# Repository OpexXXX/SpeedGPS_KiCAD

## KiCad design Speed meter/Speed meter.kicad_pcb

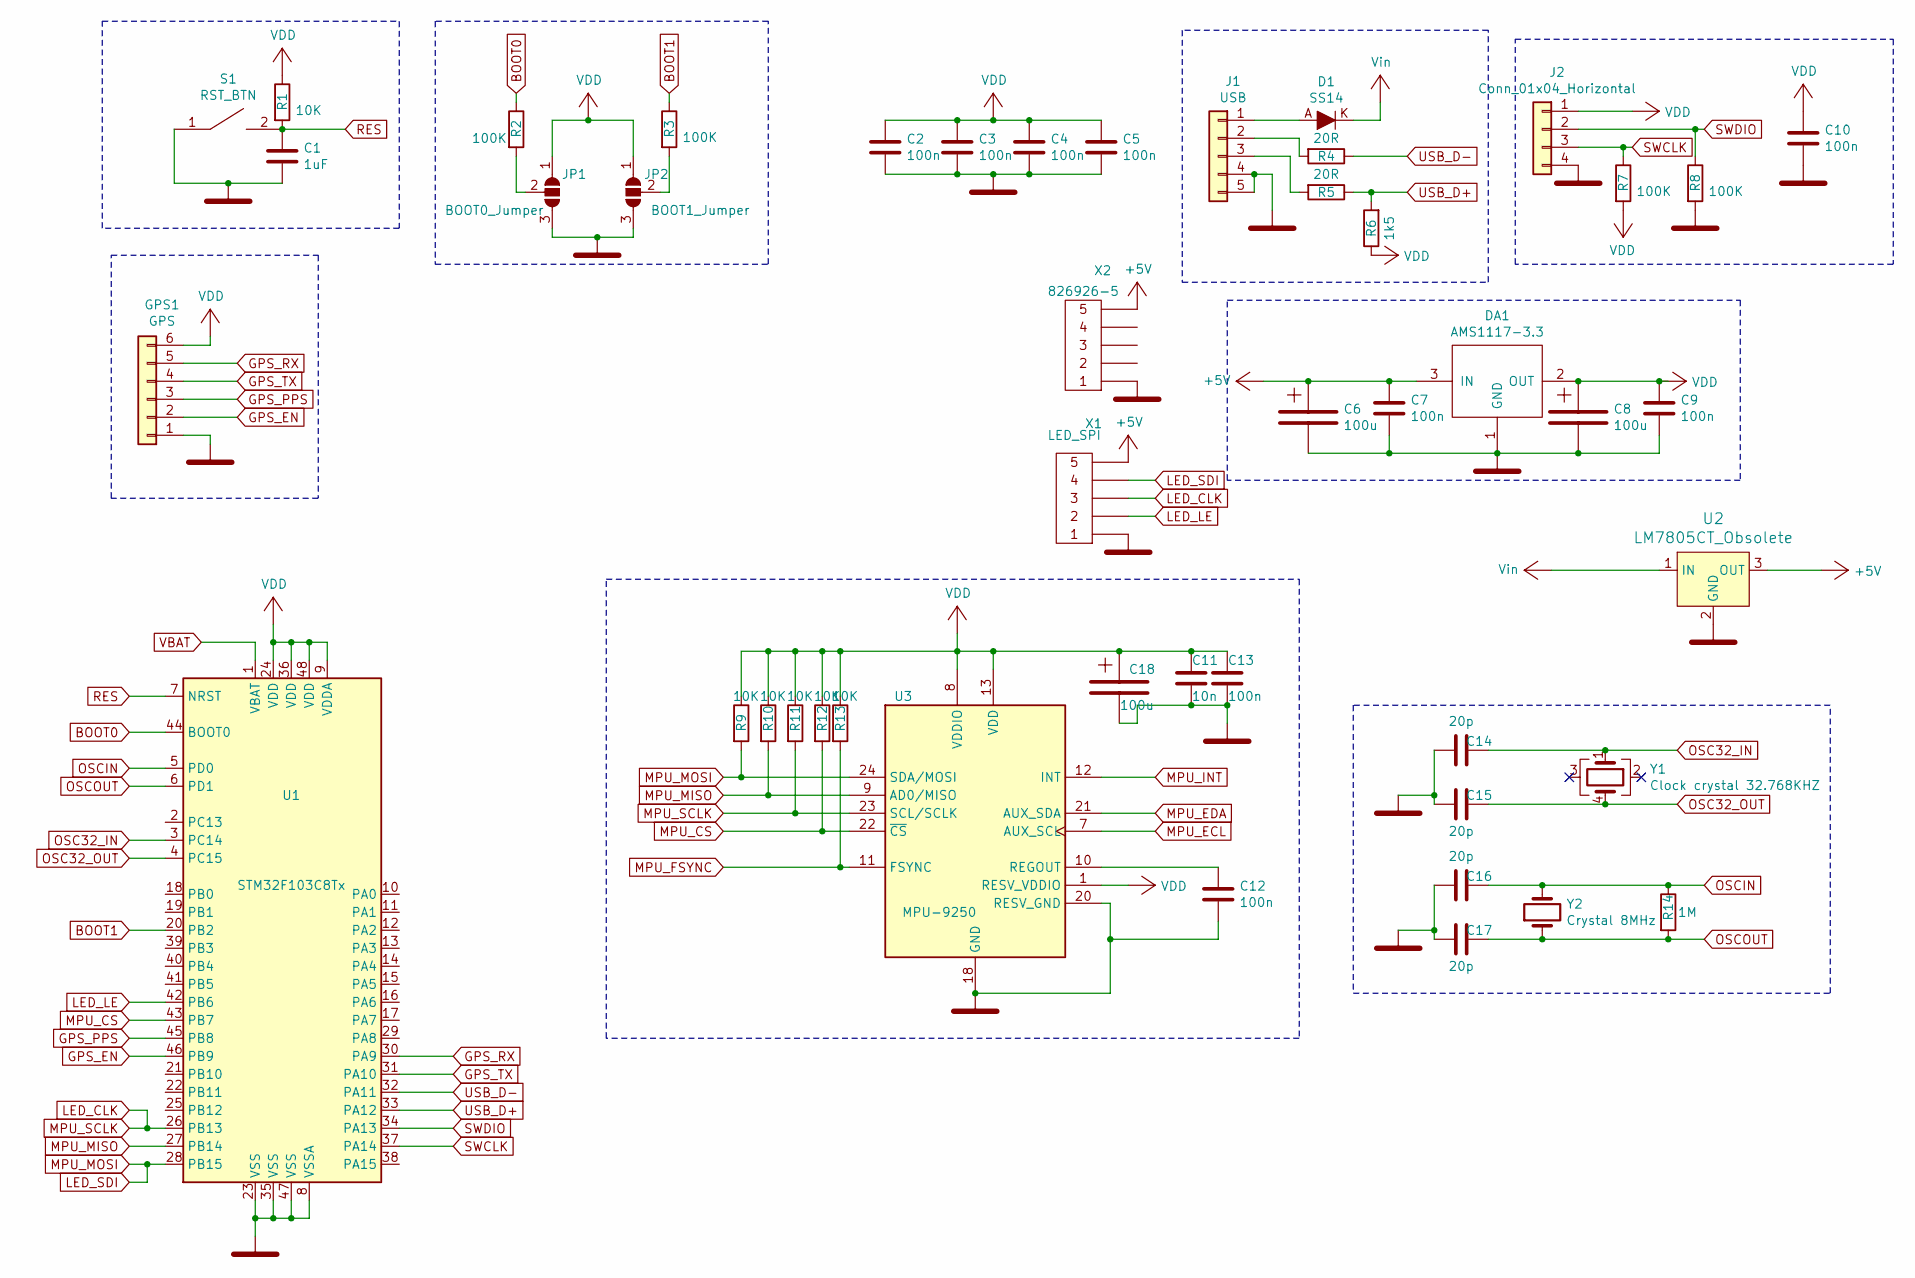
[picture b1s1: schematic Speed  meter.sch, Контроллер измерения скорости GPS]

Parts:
C1: 1uF; C_0603_1608Metric_Pad1.05x0.95mm_HandSolder
C2, C3, C4, C5, C7, C9, C10, C12, C13: 100n; C_0603_1608Metric_Pad1.05x0.95mm_HandSolder
C6, C8, C18: T491B107M010AT; CP_EIA-3528-15_AVX-H_Pad1.50x2.35mm_HandSolder
C11: 10n; C_0603_1608Metric_Pad1.05x0.95mm_HandSolder
C14, C15, C16, C17: 20p; C_0603_1608Metric_Pad1.05x0.95mm_HandSolder
D1: SS14; DO-214AC; MPN SS14; Digi-Key_PN SS14CT-ND
DA1: AMS1117-3.3; SOT-223
GPS1: GPS; PinHeader_2x03_P2.00mm_Vertical
J1: USB; PinHeader_1x05_P2.00mm_Vertical
J2: Conn_01x04_Horizontal; PinHeader_1x04_P2.54mm_Horizontal
JP1: BOOT0_Jumper; SolderJumper-3_P1.3mm_Open_RoundedPad1.0x1.5mm_NumberLabels
JP2: BOOT1_Jumper; SolderJumper-3_P1.3mm_Open_RoundedPad1.0x1.5mm_NumberLabels
R1, R9, R10, R11, R12, R13: 10K; R_0603_1608Metric_Pad1.05x0.95mm_HandSolder
R2, R3, R7, R8: 100K; R_0603_1608Metric_Pad1.05x0.95mm_HandSolder
R4, R5: 20R; R_0603_1608Metric_Pad1.05x0.95mm_HandSolder
R6: 1k5; R_0603_1608Metric_Pad1.05x0.95mm_HandSolder
R14: 1M; R_0603_1608Metric_Pad1.05x0.95mm_HandSolder
S1: RST_BTN; TS-1185-C-A-A
U1: STM32F103C8Tx; LQFP-48_7x7mm_P0.5mm
U2: LM7805CT_Obsolete; TO-220-3_Vertical; MPN LM7805CT; Digi-Key_PN LM7805CT-ND
U3: MPU-9250; InvenSense_QFN-24_3x3mm_P0.4mm
X1: LED_SPI; PinHeader_1x05_P2.54mm_Vertical
X2: 826926-5; PinHeader_1x05_P2.54mm_Vertical
Y1: Clock crystal 32.768KHZ; Oscillator_SMD_Fordahl_DFAS2-4Pin_7.3x5.1mm_HandSoldering
Y2: Crystal 8MHz; Crystal_HC18-U_Vertical

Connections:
+5V: C6.1, C7.1, DA1.3 (IN), U2.3 (OUT), X1.5, X2.5
BOOT0: R2.1, U1.44 (BOOT0)
BOOT1: R3.1, U1.20 (PB2)
GND: C1.2, C2.2, C3.2, C4.2, C5.2, C6.2, C7.2, C8.2, C9.2, C10.2, C11.2, C12.2, C13.2, C14.2, C15.2, C16.2, C17.2, C18.2, DA1.1 (GND), GPS1.1, J1.4, J1.5, J2.4, JP1.3 (B), JP2.3 (B), R8.2, S1.1, U1.8 (VSSA), U1.23 (VSS), U1.35 (VSS), U1.47 (VSS), U2.2 (GND), U3.18 (GND), U3.20 (RESV_GND), X1.1, X2.1
GPS_EN: GPS1.2, U1.46 (PB9)
GPS_PPS: GPS1.3, U1.45 (PB8)
GPS_RX: GPS1.5, U1.30 (PA9)
GPS_TX: GPS1.4, U1.31 (PA10)
LED_CLK: R11.2, U1.26 (PB13), U3.23 (SCL/SCLK), X1.3
LED_LE: U1.42 (PB6), X1.2
LED_SDI: R9.2, U1.28 (PB15), U3.24 (SDA/MOSI), X1.4
MPU_CS: R12.2, U1.43 (PB7), U3.22 (~CS)
MPU_ECL: U3.7 (AUX_SCL)
MPU_EDA: U3.21 (AUX_SDA)
MPU_FSYNC: R13.2, U3.11 (FSYNC)
MPU_INT: U3.12 (INT)
MPU_MISO: R10.2, U1.27 (PB14), U3.9 (AD0/MISO)
unnamed: C12.1, U3.10 (REGOUT)
unnamed: D1.A, J1.1
unnamed: J1.2, R4.2
unnamed: J1.3, R5.2
unnamed: JP1.2 (C), R2.2
unnamed: JP2.2 (C), R3.2
OSC32_IN: C14.1, U1.3 (PC14), Y1.1
OSC32_OUT: C15.1, U1.4 (PC15), Y1.4
OSCIN: C16.1, R14.1, U1.5 (PD0), Y2.2
OSCOUT: C17.1, R14.2, U1.6 (PD1), Y2.1
RES: C1.1, R1.2, S1.2, U1.7 (NRST)
SWCLK: J2.3, R7.1, U1.37 (PA14)
SWDIO: J2.2, R8.1, U1.34 (PA13)
USB_D+: R5.1, R6.2, U1.33 (PA12)
USB_D-: R4.1, U1.32 (PA11)
VBAT: U1.1 (VBAT)
VDD: C2.1, C3.1, C4.1, C5.1, C8.1, C9.1, C10.1, C11.1, C13.1, C18.1, DA1.2 (OUT), GPS1.6, J2.1, JP1.1 (A), JP2.1 (A), R1.1, R6.1, R7.2, R9.1, R10.1, R11.1, R12.1, R13.1, U1.9 (VDDA), U1.24 (VDD), U1.36 (VDD), U1.48 (VDD), U3.1 (RESV_VDDIO), U3.8 (VDDIO), U3.13 (VDD)
Vin: D1.K, U2.1 (IN)

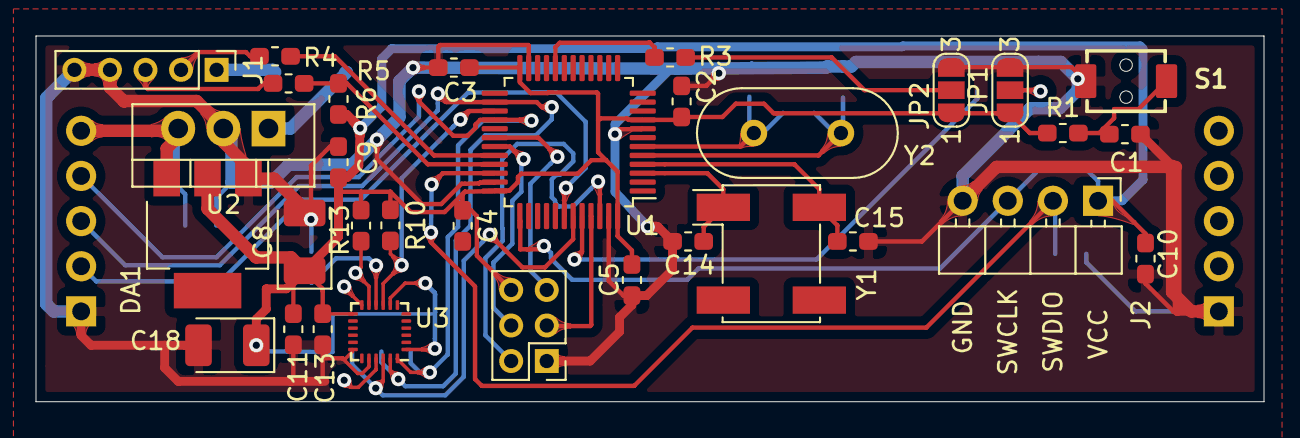
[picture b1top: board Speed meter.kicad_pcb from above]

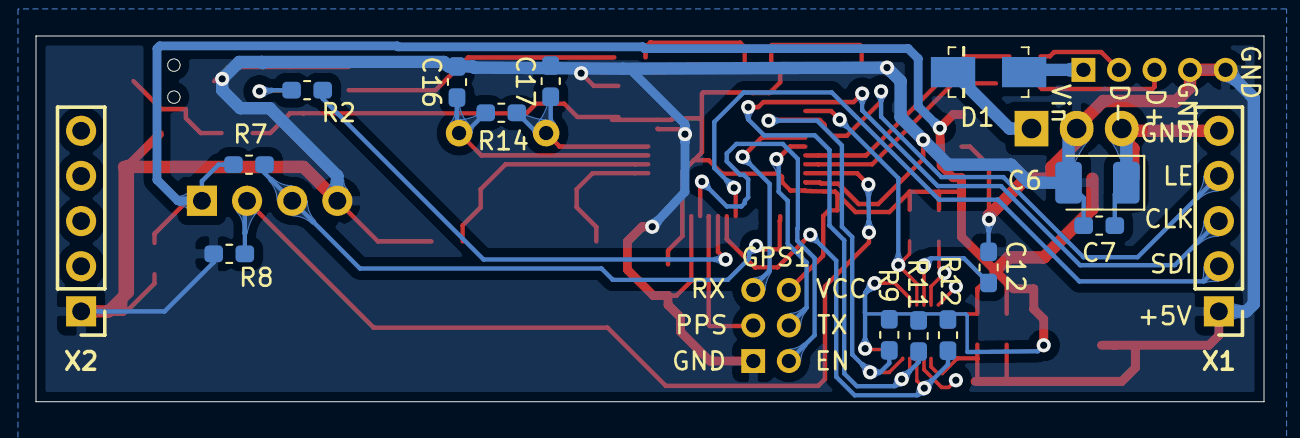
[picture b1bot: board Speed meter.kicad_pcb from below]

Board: 2 copper layers, 69.1 x 20.6 mm, 47 parts (15 on the bottom side), 31 nets.

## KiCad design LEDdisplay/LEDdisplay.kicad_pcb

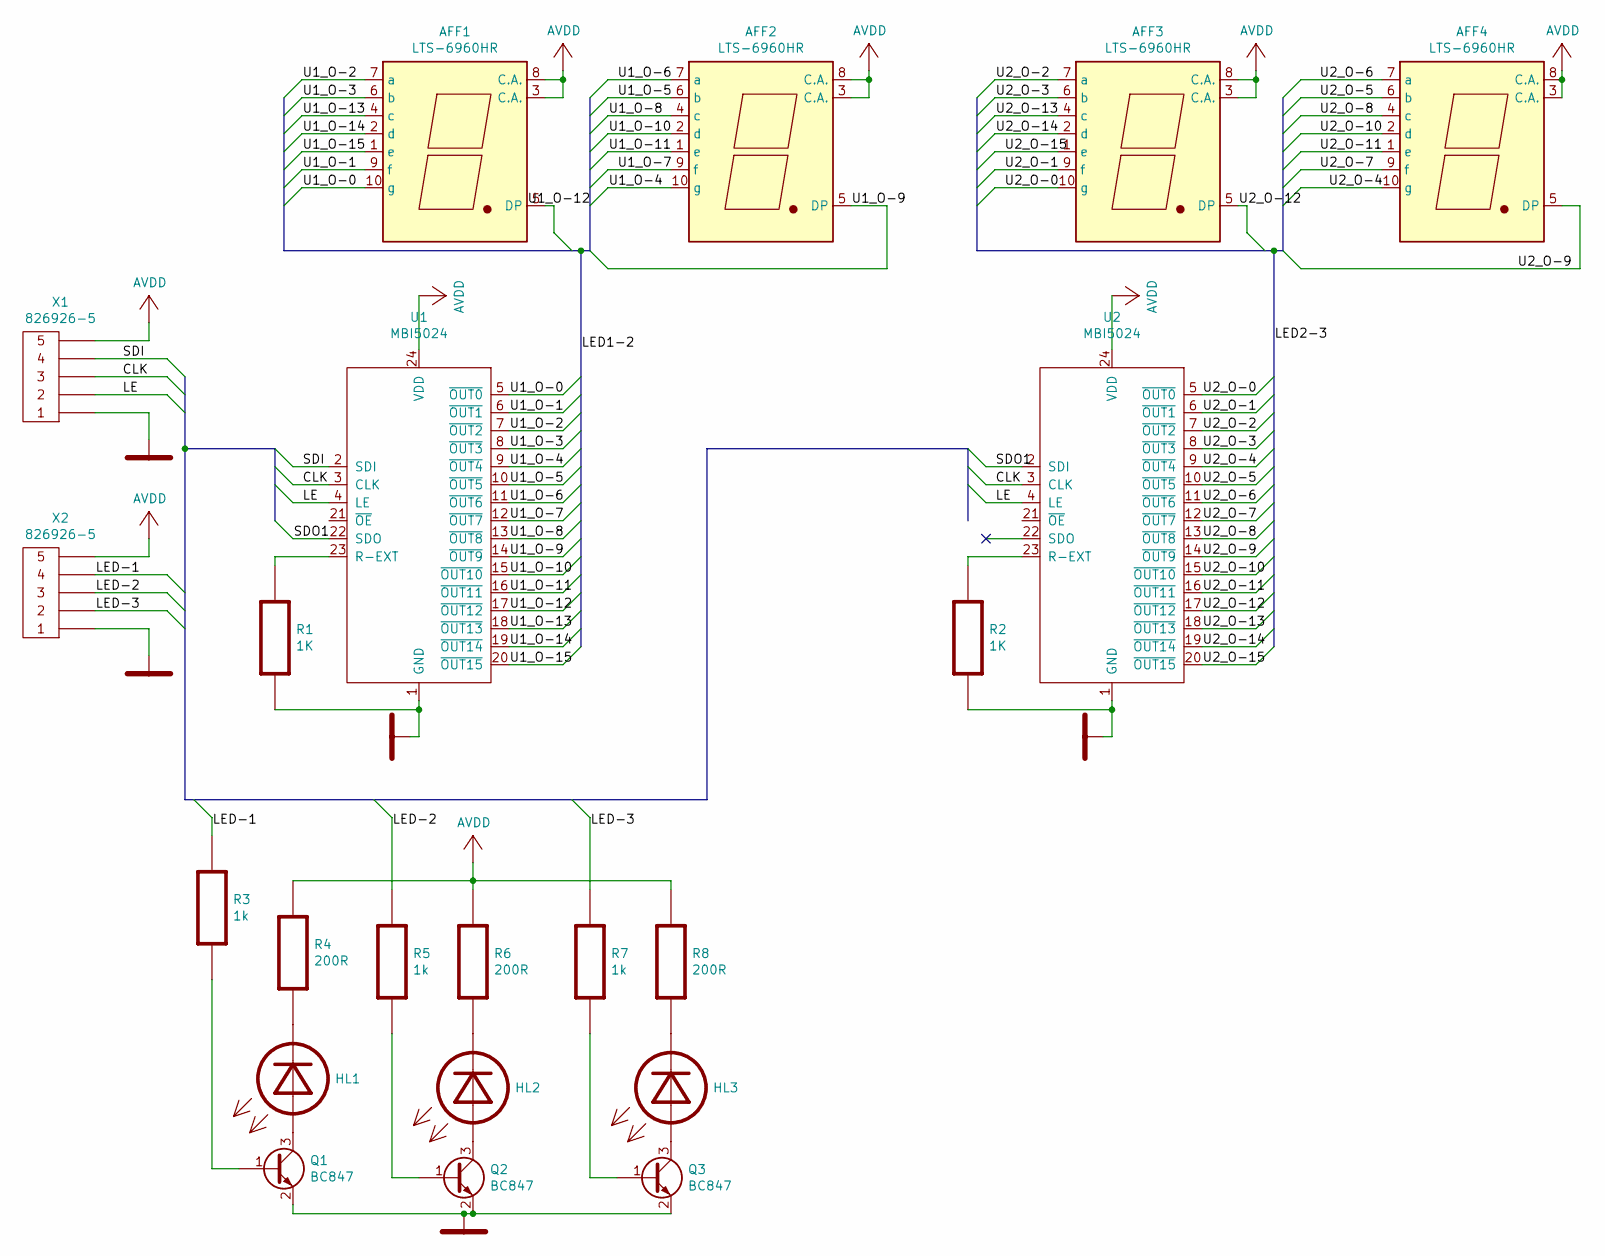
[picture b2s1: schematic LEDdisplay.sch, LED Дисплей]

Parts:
AFF1, AFF2, AFF3, AFF4: LTS-6960HR; 7SegmentLED_LTS6760_LTS6780
HL1, HL2, HL3: FC-DA1608BK-470H10; LED_0805_2012Metric_Pad1.15x1.40mm_HandSolder
Q1, Q2, Q3: BC847; SOT-23
R1, R2: 1K; R_0805_2012Metric_Pad1.15x1.40mm_HandSolder; ManufacturerPartNumber RC0805FR-0722RL
R3, R5, R7: 1k; R_0805_2012Metric_Pad1.15x1.40mm_HandSolder; ManufacturerPartNumber RC0805FR-0722RL
R4, R6, R8: 200R; R_0805_2012Metric_Pad1.15x1.40mm_HandSolder; ManufacturerPartNumber RC0805FR-0722RL
U1: MBI5024; SSOP-24_3.9x8.7mm_P0.635mm
U2: MBI5024; SSOP-24-1mm
X1, X2: 826926-5; PinSocket_1x05_P2.54mm_Vertical

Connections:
/CLK: U1.3 (CLK), U2.3 (CLK), X1.3
/LE: U1.4 (LE), U2.4 (LE), X1.2
/LED-1: R3.1, X2.4
/LED-2: R5.1, X2.3
/LED-3: R7.1, X2.2
/SDI: U1.2 (SDI), X1.4
/SDO1: U1.22 (SDO), U2.2 (SDI)
/U1_O-0: AFF1.10 (g), U1.5 (~OUT0)
/U1_O-1: AFF1.9 (f), U1.6 (~OUT1)
/U1_O-2: AFF1.7 (a), U1.7 (~OUT2)
/U1_O-3: AFF1.6 (b), U1.8 (~OUT3)
/U1_O-4: AFF2.10 (g), U1.9 (~OUT4)
/U1_O-5: AFF2.6 (b), U1.10 (~OUT5)
/U1_O-6: AFF2.7 (a), U1.11 (~OUT6)
/U1_O-7: AFF2.9 (f), U1.12 (~OUT7)
/U1_O-8: AFF2.4 (c), U1.13 (~OUT8)
/U1_O-9: AFF2.5 (DP), U1.14 (~OUT9)
/U1_O-10: AFF2.2 (d), U1.15 (~OUT10)
/U1_O-11: AFF2.1 (e), U1.16 (~OUT11)
/U1_O-12: U1.17 (~OUT12)
/U1_O-13: AFF1.4 (c), U1.18 (~OUT13)
/U1_O-14: AFF1.2 (d), U1.19 (~OUT14)
/U1_O-15: AFF1.1 (e), U1.20 (~OUT15)
/U2_O-0: AFF3.10 (g), U2.5 (~OUT0)
/U2_O-1: AFF3.9 (f), U2.6 (~OUT1)
/U2_O-2: AFF3.7 (a), U2.7 (~OUT2)
/U2_O-3: AFF3.6 (b), U2.8 (~OUT3)
/U2_O-4: AFF4.10 (g), U2.9 (~OUT4)
/U2_O-5: AFF4.6 (b), U2.10 (~OUT5)
/U2_O-6: AFF4.7 (a), U2.11 (~OUT6)
/U2_O-7: AFF4.9 (f), U2.12 (~OUT7)
/U2_O-8: AFF4.4 (c), U2.13 (~OUT8)
/U2_O-9: AFF4.5 (DP), U2.14 (~OUT9)
/U2_O-10: AFF4.2 (d), U2.15 (~OUT10)
/U2_O-11: AFF4.1 (e), U2.16 (~OUT11)
/U2_O-12: AFF3.5 (DP), U2.17 (~OUT12)
/U2_O-13: AFF3.4 (c), U2.18 (~OUT13)
/U2_O-14: AFF3.2 (d), U2.19 (~OUT14)
/U2_O-15: AFF3.1 (e), U2.20 (~OUT15)
AVDD: AFF1.3 (C.A.), AFF1.8 (C.A.), AFF2.3 (C.A.), AFF2.8 (C.A.), AFF3.3 (C.A.), AFF3.8 (C.A.), AFF4.3 (C.A.), AFF4.8 (C.A.), R4.1, R6.1, R8.1, U1.24 (VDD), U2.24 (VDD), X1.5, X2.5
GND: Q1.2 (E), Q2.2 (E), Q3.2 (E), R1.2, R2.2, U1.1 (GND), U2.1 (GND), X1.1, X2.1
unnamed: HL1.1 (K), R4.2
unnamed: HL1.2 (A), Q1.3 (C)
unnamed: HL2.1 (K), R6.2
unnamed: HL2.2 (A), Q2.3 (C)
unnamed: HL3.1 (K), R8.2
unnamed: HL3.2 (A), Q3.3 (C)
unnamed: Q1.1 (B), R3.2
unnamed: Q2.1 (B), R5.2
unnamed: Q3.1 (B), R7.2
unnamed: R1.1, U1.23 (R-EXT)
unnamed: R2.1, U2.23 (R-EXT)

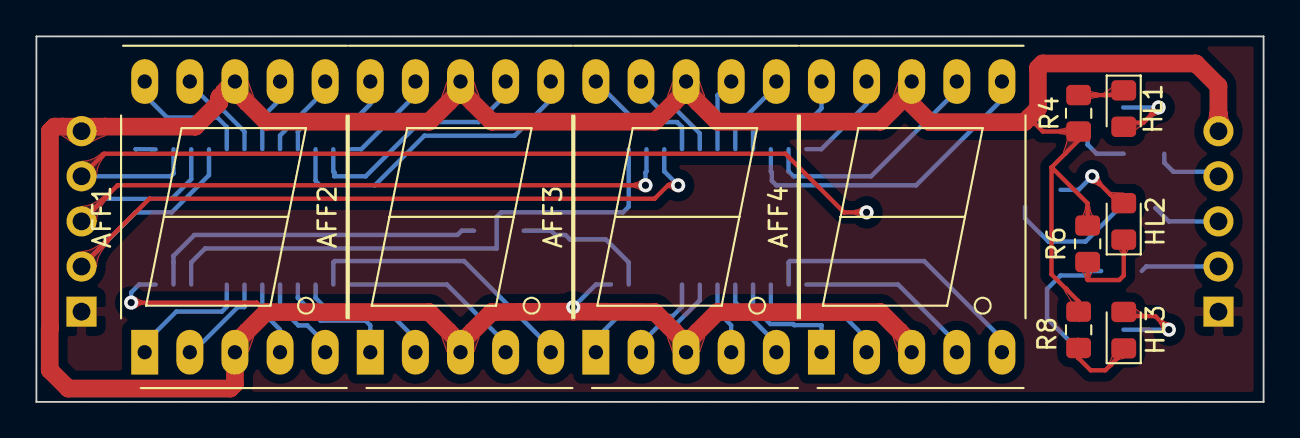
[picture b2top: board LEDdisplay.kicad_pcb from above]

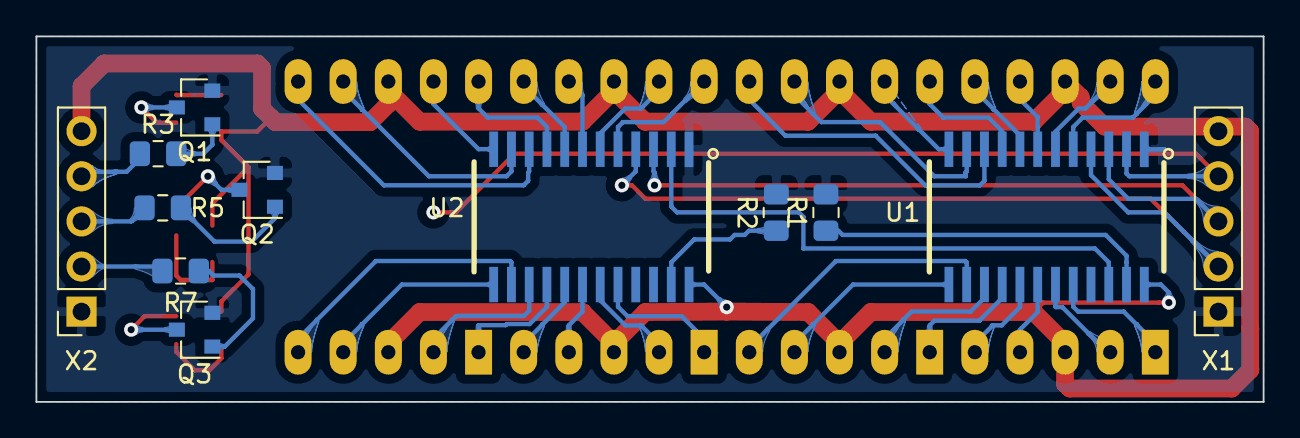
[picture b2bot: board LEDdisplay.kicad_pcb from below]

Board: 2 copper layers, 69.1 x 20.6 mm, 22 parts (12 on the bottom side), 51 nets.

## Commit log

2020-03-09 Initial
